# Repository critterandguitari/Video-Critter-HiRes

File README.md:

Video-Critter-HiRes
===================

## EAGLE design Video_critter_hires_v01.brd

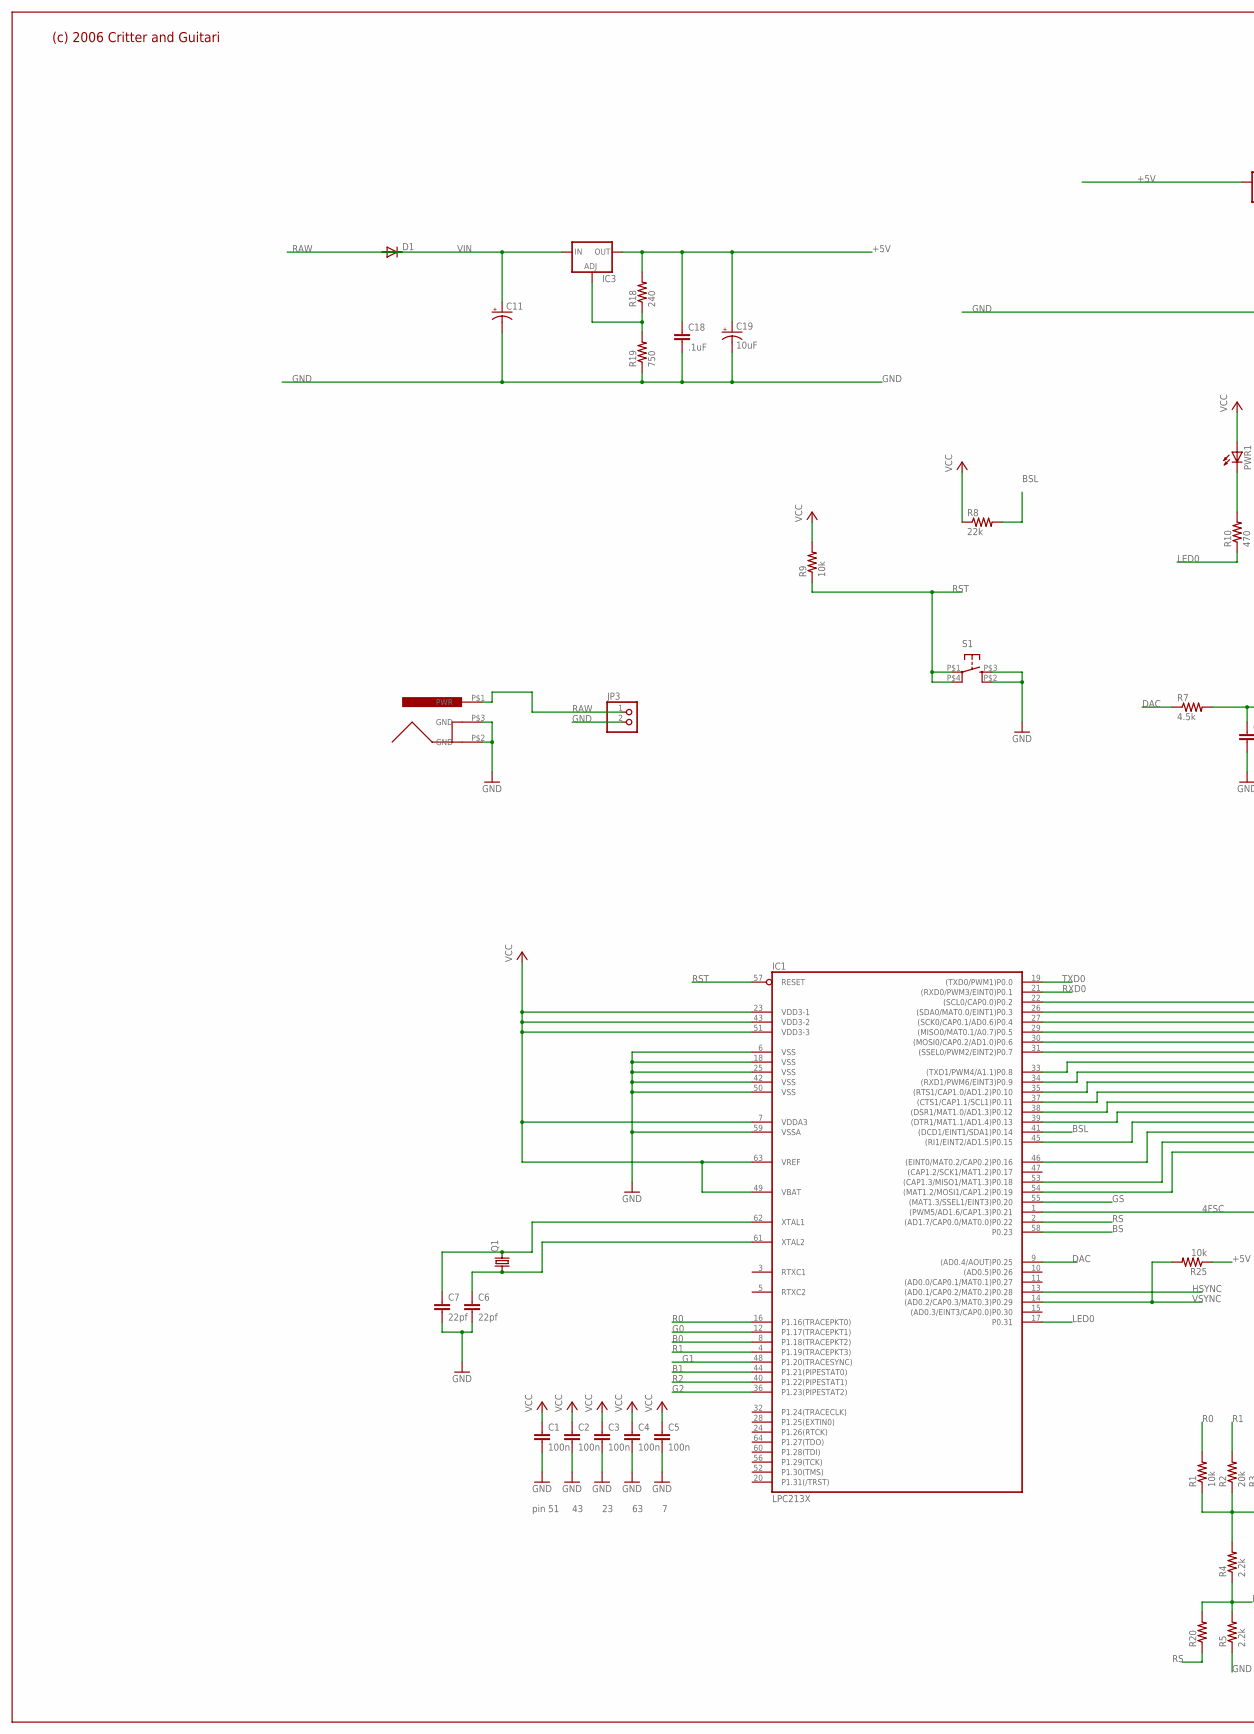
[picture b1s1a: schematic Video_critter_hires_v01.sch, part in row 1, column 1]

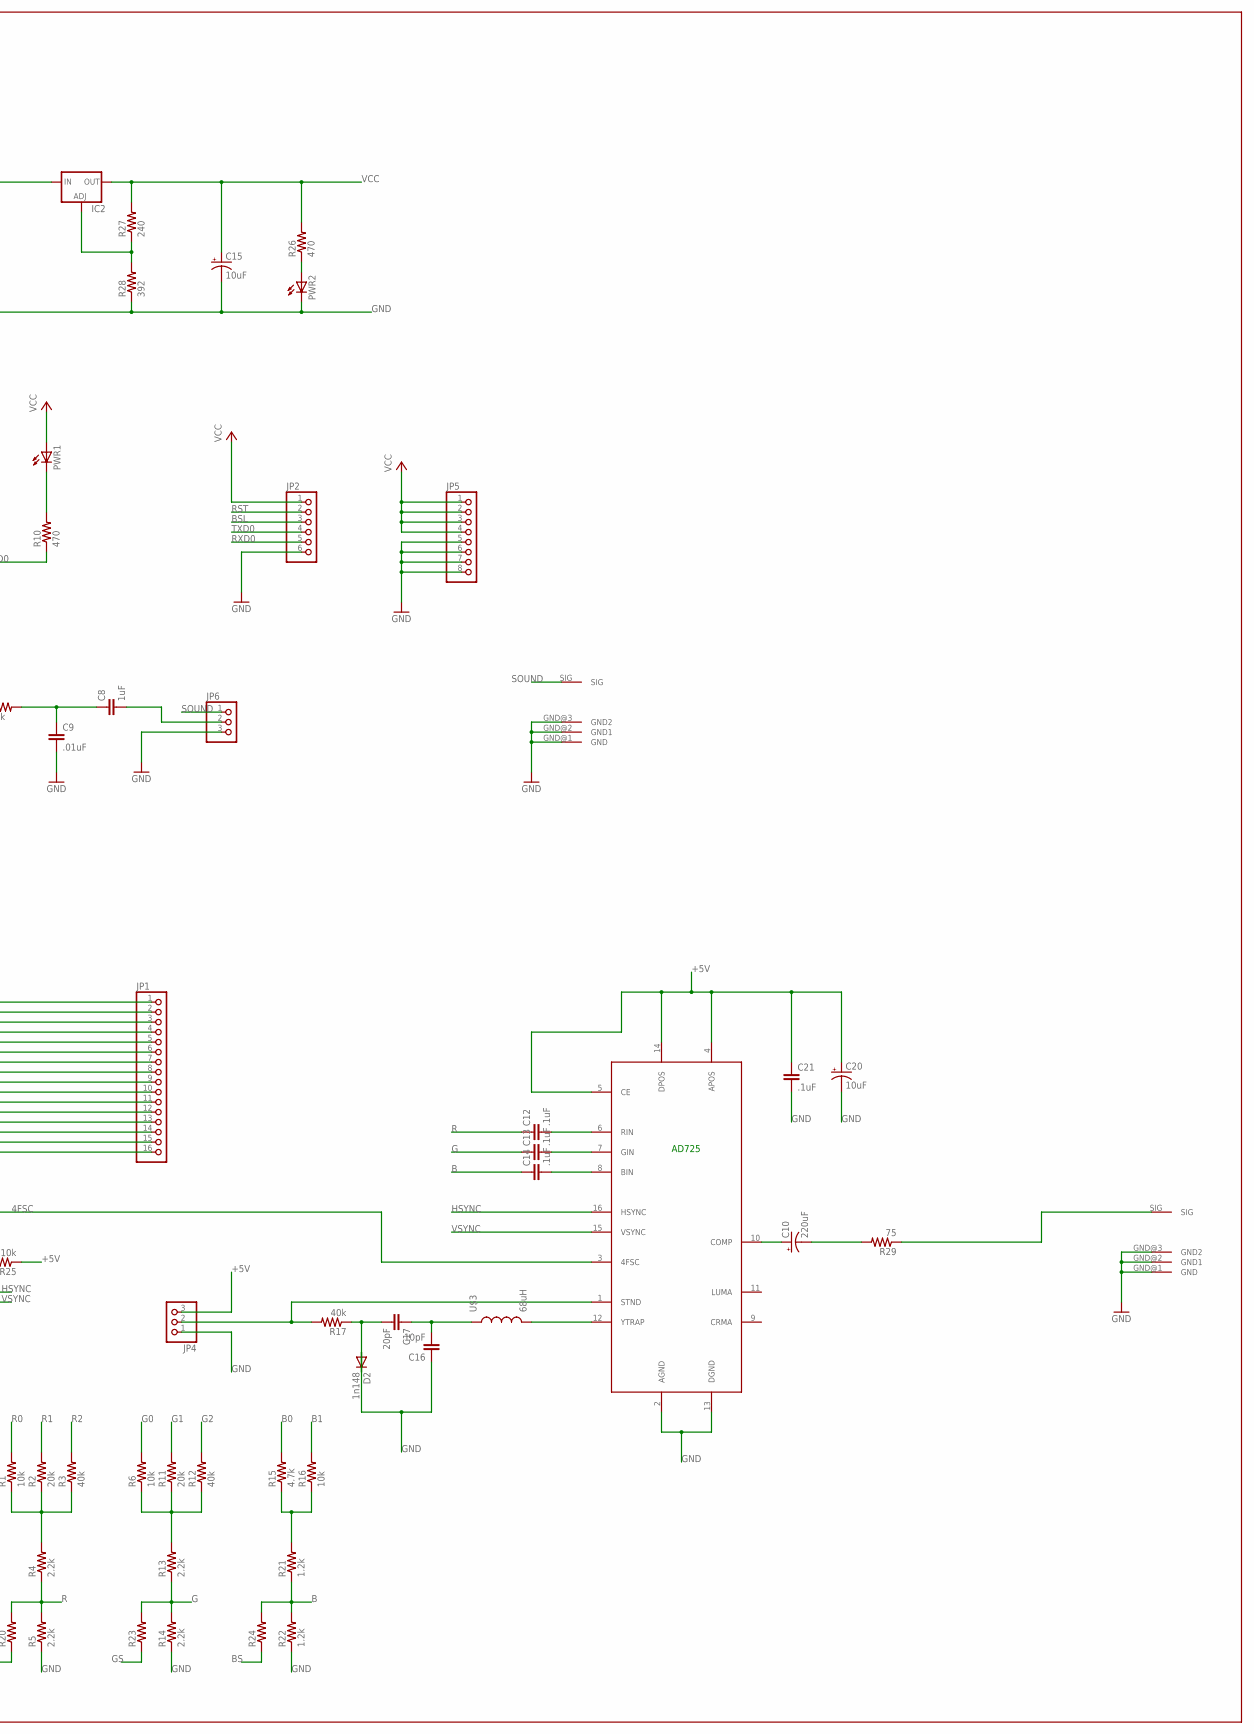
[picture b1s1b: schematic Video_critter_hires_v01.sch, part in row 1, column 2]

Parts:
C1, C2, C3, C4, C5: 100n; C0603
C6, C7: 22pf; C0603
C8: 1uF; C0603
C9: .01uF; C0603
C10: 220uF; PANASONIC_D
C11: CPOL-USE3.5-8; E3,5-8
C12, C13, C14, C18, C21: .1uF; C0603
C15, C19, C20: 10uF; CPOL_1206
C16: 10pF; C0603
C17: 20pF; C0603
D1: DIODESMB; SMB
D2: 1n148; SOD323-W
IC1: LPC213X; SQFP-S-10X10-64
IC2, IC3: V_REG_FAN1117SOT223; SOT223
JP1: PINHD-1X16; 1X16
JP2: PINHD-1X6; 1X06
JP3: PINHD-1X2; 1X02
JP4, JP6: PINHD-1X3; 1X03
JP5: PINHD-1X8; 1X08
PWR1, PWR2: LED1206; CHIPLED_1206
Q1: CRYSTALSOCKETED; HC49U-SOCKETED
R1, R6, R9, R16, R25: 10k; R0603
R2, R11: 20k; R0603
R3, R12, R17: 40k; R0603
R4, R5, R13, R14: 2.2k; R0603
R7: 4.5k; R0603
R8: 22k; R0603
R10, R26: 470; R0603
R15: 4.7k; R0603
R18, R27: 240; R0603
R19: 750; R0603
R20, R23, R24: RES0603; R0603
R21, R22: 1.2k; R0603
R28: 392; R0603
R29: 75; R0603
S1: TAC_SWITCH; TACTILE_SWITCH_SMD
U$1: POWER_JACK
U$2: AD725; SO16L
U$3: 68uH; INDUCTOR_SMALL
U$5, U$7: PHONO_PLUG; PHONO_PCB

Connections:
4FSC: IC1.1 ((PWM5/AD1.6/CAP1.3)P0.21), U$2.3 (4FSC)
+5V: C18.1, C19.A (+), C20.A (+), C21.1, IC2.3 (IN), IC3.2 (OUT), JP4.3, R18.2, R25.1, U$2.4 (APOS), U$2.5 (CE), U$2.14 (DPOS)
B: C14.1, R21.1, R22.2, R24.2
B0: IC1.8 (P1.18(TRACEPKT2)), R15.2
B1: IC1.44 (P1.21(PIPESTAT0)), R16.2
BS: IC1.58 (P0.23), R24.1
BSL: IC1.41 ((DCD1/EINT1/SDA1)P0.14), JP2.3, R8.2
BURST: IC1.31 ((SSEL0/PWM2/EINT2)P0.7), JP1.6
DAC: IC1.9 ((AD0.4/AOUT)P0.25), R7.1
G: C13.1, R13.1, R14.2, R23.2
G0: IC1.12 (P1.17(TRACEPKT1)), R6.2
G1: IC1.48 (P1.20(TRACESYNC)), R11.2
G2: IC1.36 (P1.23(PIPESTAT2)), R12.2
GND: C1.2, C2.2, C3.2, C4.2, C5.2, C6.2, C7.2, C9.2, C11.-, C15.C (-), C16.1, C18.2, C19.C (-), C20.C (-), C21.2, D2.A, IC1.6 (VSS), IC1.18 (VSS), IC1.25 (VSS), IC1.42 (VSS), IC1.50 (VSS), IC1.59 (VSSA), JP2.6, JP3.2, JP4.1, JP5.5, JP5.6, JP5.7, JP5.8, JP6.3, PWR2.C, R5.1, R14.1, R19.1, R22.1, R28.1, S1.P$2 (S1), S1.P$3 (S), U$1.P$2 (GND), U$1.P$3 (GND), U$2.2 (AGND), U$2.13 (DGND), U$5.GND@1 (GND), U$5.GND@2 (GND1), U$5.GND@3 (GND2), U$7.GND@1 (GND), U$7.GND@2 (GND1), U$7.GND@3 (GND2)
GS: IC1.55 ((MAT1.3/SSEL1/EINT3)P0.20), R23.1
HSYNC: IC1.13 ((AD0.1/CAP0.2/MAT0.2)P0.28), U$2.16 (HSYNC)
LED0: IC1.17 (P0.31), R10.1
unnamed: C8.1, C9.1, R7.2
unnamed: C7.1, IC1.62 (XTAL1), Q1.2
unnamed: C6.1, IC1.61 (XTAL2), Q1.1
unnamed: PWR1.C, R10.2
unnamed: C10.+, U$2.10 (COMP)
unnamed: IC1.22 ((SCL0/CAP0.0)P0.2), JP1.1
unnamed: C8.2, JP6.2
unnamed: C12.2, U$2.6 (RIN)
unnamed: IC1.26 ((SDA0/MAT0.0/EINT1)P0.3), JP1.2
unnamed: IC1.27 ((SCK0/CAP0.1/AD0.6)P0.4), JP1.3
unnamed: IC3.1 (ADJ), R18.1, R19.2
unnamed: IC1.29 ((MISO0/MAT0.1/A0.7)P0.5), JP1.4
unnamed: IC1.30 ((MOSI0/CAP0.2/AD1.0)P0.6), JP1.5
unnamed: C13.2, U$2.7 (GIN)
unnamed: IC1.33 ((TXD1/PWM4/A1.1)P0.8), JP1.7
unnamed: IC1.34 ((RXD1/PWM6/EINT3)P0.9), JP1.8
unnamed: IC1.35 ((RTS1/CAP1.0/AD1.2)P0.10), JP1.9
unnamed: IC1.37 ((CTS1/CAP1.1/SCL1)P0.11), JP1.10
unnamed: IC1.38 ((DSR1/MAT1.0/AD1.3)P0.12), JP1.11
unnamed: IC1.39 ((DTR1/MAT1.1/AD1.4)P0.13), JP1.12
unnamed: IC1.45 ((RI1/EINT2/AD1.5)P0.15), JP1.13
unnamed: IC1.46 ((EINT0/MAT0.2/CAP0.2)P0.16), JP1.14
unnamed: IC1.53 ((CAP1.3/MISO1/MAT1.3)P0.18), JP1.15
unnamed: U$2.12 (YTRAP), U$3.P$2 (2)
unnamed: IC1.54 ((MAT1.2/MOSI1/CAP1.2)P0.19), JP1.16
unnamed: C14.2, U$2.8 (BIN)
unnamed: R1.1, R2.1, R3.1, R4.2
unnamed: R29.1, U$7.SIG
unnamed: R6.1, R11.1, R12.1, R13.2
unnamed: PWR2.A, R26.1
unnamed: R15.1, R16.1, R21.2
unnamed: IC2.1 (ADJ), R27.1, R28.2
unnamed: C16.2, C17.1, U$3.P$1 (1)
unnamed: C17.2, D2.C, R17.1
unnamed: JP4.2, R17.2, U$2.1 (STND)
unnamed: C10.-, R29.2
R: C12.1, R4.1, R5.2, R20.2
R0: IC1.16 (P1.16(TRACEPKT0)), R1.2
R1: IC1.4 (P1.19(TRACEPKT3)), R2.2
R2: IC1.40 (P1.22(PIPESTAT1)), R3.2
RAW: D1.1 (C), JP3.1, U$1.P$1 (PWR)
RS: IC1.2 ((AD1.7/CAP0.0/MAT0.0)P0.22), R20.1
RST: IC1.57 (RESET), JP2.2, R9.1, S1.P$1, S1.P$4 (P1)
RXD0: IC1.21 ((RXD0/PWM3/EINT0)P0.1), JP2.5
SOUND: JP6.1, U$5.SIG
TXD0: IC1.19 ((TXD0/PWM1)P0.0), JP2.4
VCC: C1.1, C2.1, C3.1, C4.1, C5.1, C15.A (+), IC1.7 (VDDA3), IC1.23 (VDD3-1), IC1.43 (VDD3-2), IC1.49 (VBAT), IC1.51 (VDD3-3), IC1.63 (VREF), IC2.2 (OUT), JP2.1, JP5.1, JP5.2, JP5.3, JP5.4, PWR1.A, R8.1, R9.2, R26.2, R27.2
VIN: C11.+, D1.2 (A), IC3.3 (IN)
VSYNC: IC1.14 ((AD0.2/CAP0.3/MAT0.3)P0.29), R25.2, U$2.15 (VSYNC)

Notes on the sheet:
pin 51
AD725
(c) 2006 Critter and Guitari

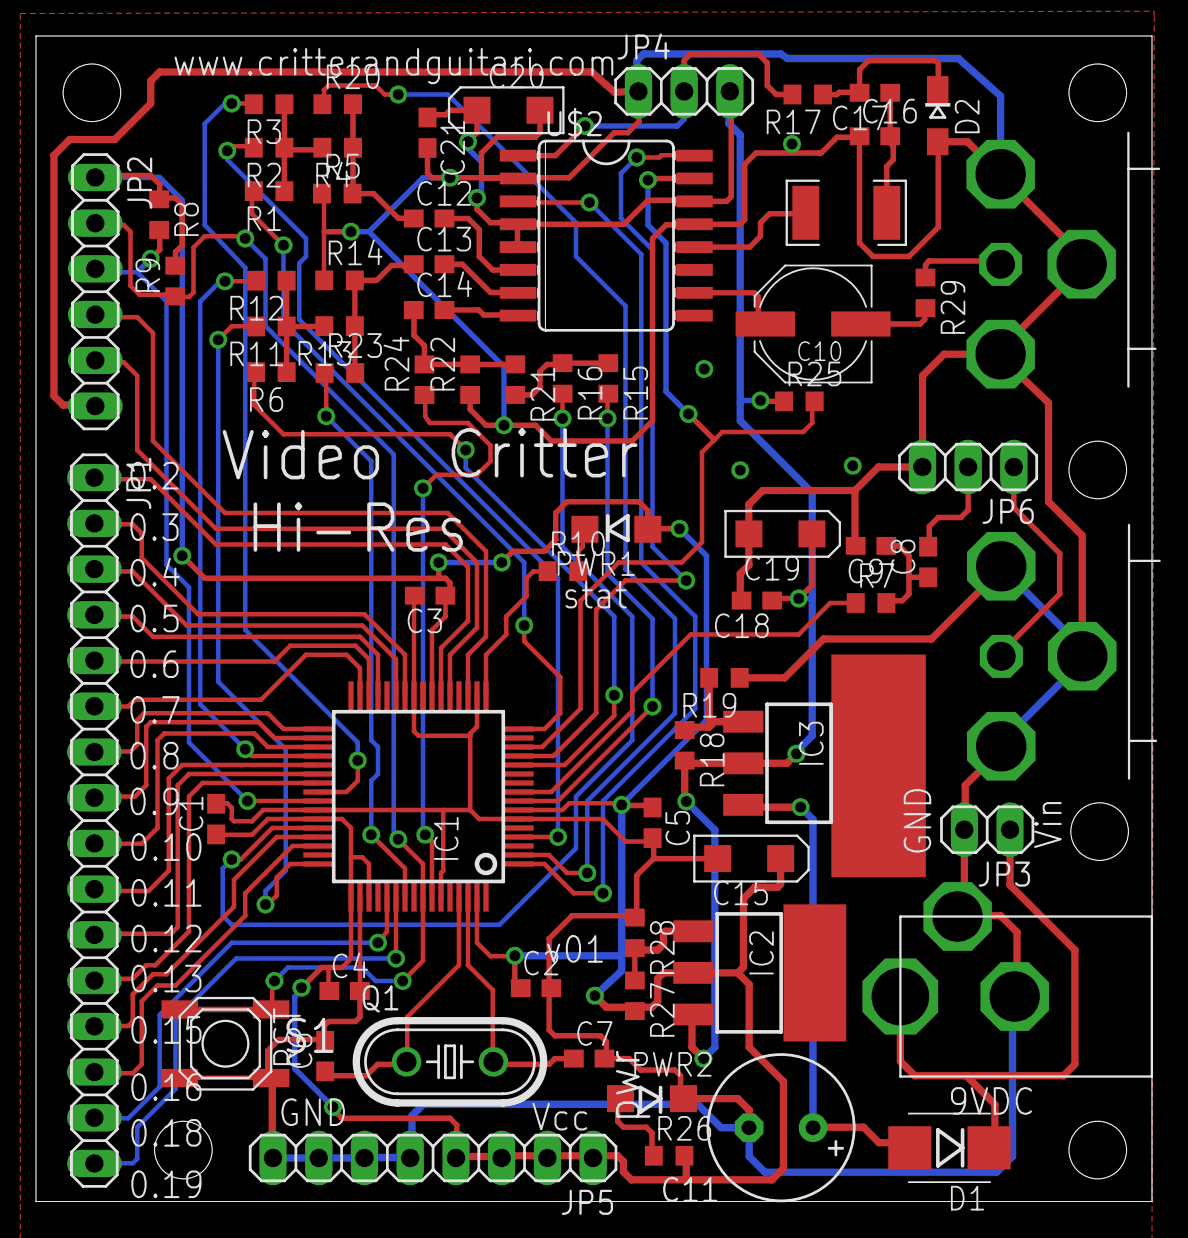
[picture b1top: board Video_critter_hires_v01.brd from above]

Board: 2 copper layers, 62.0 x 64.8 mm, 70 parts (0 on the bottom side), 66 nets.

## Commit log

2013-04-21 adding eagle files
